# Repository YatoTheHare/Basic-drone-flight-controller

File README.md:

*[PL version]*
# Podstawowy kontroler lotu drona na ESP32-S3-WROOM1

## Opis układu

Jednowarstwowa płytka PCB (z kilkoma przelotkami na zworki łączące wyspy GND).
Układ przeznaczony jest do pełnienia funkcji kontrolera lotu drona czterowirnikowego.
W skład układu wchodzą:
- Port USB-C dla zasilania 5V DC oraz transferu danych
- Mikrokontroler ESP32-S3-WROOM1 z gniazdem JST-SH dla urządzenia peryferyjnego IIC
- Inercyjna 6-osiowa jednostka pomiarowa BMI270
- Układ step-down z 5V na 3,3V - TPS62A02
- Zabezpieczenie łączy danych USB przed wyładowaniami elektrostatycznymi - USBLC6-2SC6
- Dedykowane pady lutownicze dla przewodów ESC

## Cechy układu
- Pojedyncza warstwa PCB: możliwie tanie i proste wykonanie ręczne
- Możliwie kompaktowy rozmiar płytki: minimalizacja powierzchni i masy
- Wygodne umieszczenie złączy (USB-C, JST-SH, ESC)
- Gniazdo USB-C wraz z zabezpieczeniem ESD umieszczone możliwie blisko mikrokontrolera, linie danych daleko od miedzi
- Antena mikrokontrolera poza laminatem: redukcja masy i wymiarów laminatu, brak przeszkody dla sygnału radiowego
- Zastosowanie popularnych wartości rezystorów i kondensatorów: minimalizacja kosztów (brak potrzeby sprowadzania elementów innych niż typowo dostępnych w pracowniach elektronicznych)
- Miejsca wiercenia do montażu w ramie drona
- IMU możliwie blisko środka płytki
- Obsługa pinu PG układu step-down: możliwość uruchomienia procedury awaryjnej lub bezprzewodowego wysłania informacji o położeniu i nachyleniu w przypadku awarii zasilania

## Dobór elementów

### step-down:
- układ: TPS62A02 - węższy zakres napięć odpowiadający wymaganiom, tryb oszczędzania energii, mniejszy pobór prądu, większa częstotliwość pracy
- cewka: 1uH - wg. datasheet
- rezystory pętli zwrotnej: R1 120K + 1,5K, R2 27K - dobrane wg. wzoru z datasheet (R1 = R2(V_out / 0,6V - 1), gdzie R2 <= 100K. Rezystory dobrano z pośród najpopularniejszych wartości w celu minimalizacji kosztów. R2 jest znacznie mniejsze niż podana przez producenta granica akceptowalności szumów.
### protokół komunikacji peryferiów
   IIC (I2C) - protokół działający na jednej wspólnej magistrali niezależnie od liczby urządzeń, komunikacja synchronizowana, mechanizm odpowiedzi ACK, adresacja urządzeń.

### IMU:
   BMI270 niższy poziom szumów, większa odporność na zakłócenia, wibracje i niedoskonałości PCB.

## Propozycje rozwoju układu:
- konstrukcja dwuwarstwowa z osobną warstwą dla GND
- rozszerzenie dostępności złączy dla dodatkowych urządzeń i protokołów komunikacji
- obsługa dodatkowej pamięci wymiennej np. microSD - przechowywanie danych zebranych podczas lotu do późniejszej analizy

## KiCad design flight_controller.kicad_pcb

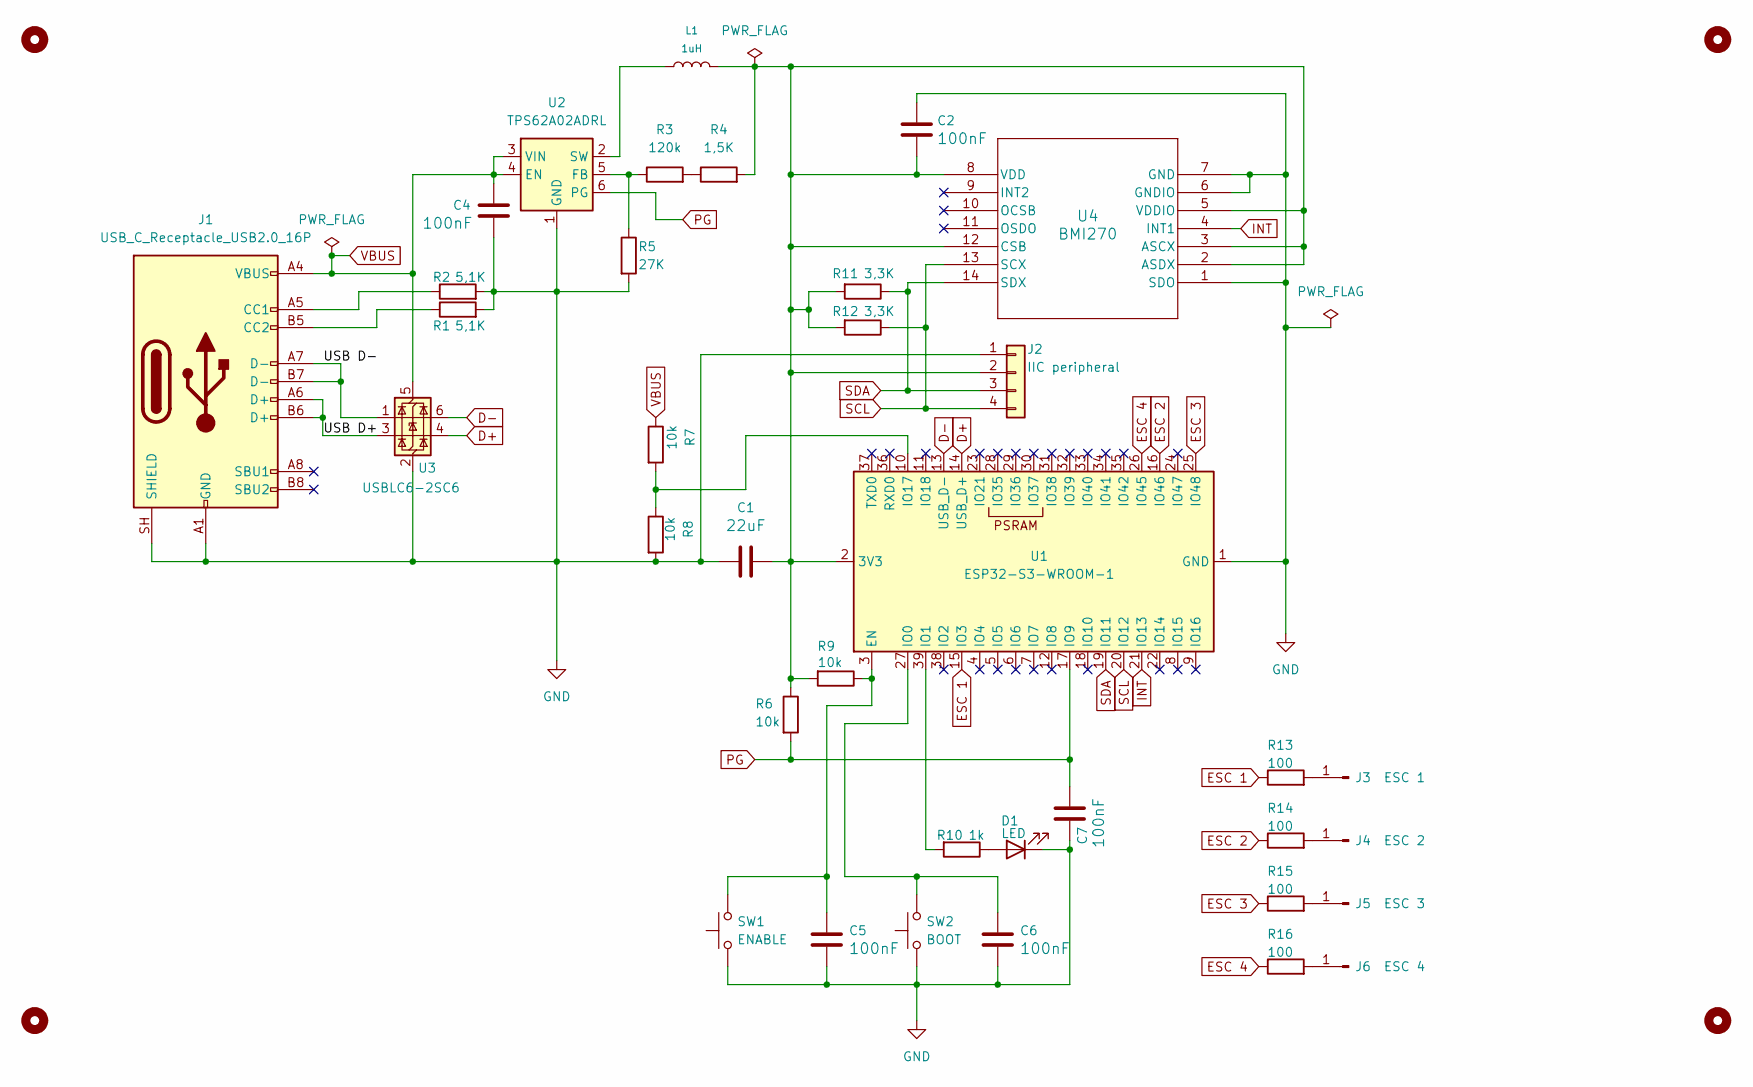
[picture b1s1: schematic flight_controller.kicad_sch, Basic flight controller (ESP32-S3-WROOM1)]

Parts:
C1: 22uF; C_0805_2012Metric_Pad1.18x1.45mm_HandSolder
C2, C4, C5, C6, C7: 100nF; C_0805_2012Metric_Pad1.18x1.45mm_HandSolder
D1: LED; LED_0603_1608Metric
H1, H2, H3, H4: MountingHole; MountingHole_2.1mm
J1: USB_C_Receptacle_USB2.0_16P; USB_C_Receptacle_HRO_TYPE-C-31-M-12
J2: IIC peripheral; JST_SH_SM04B-SRSS-TB_1x04-1MP_P1.00mm_Horizontal
J3: ESC 1; SolderWirePad_1x01_SMD_1.5x3mm
J4: ESC 2; SolderWirePad_1x01_SMD_1.5x3mm
J5: ESC 3; SolderWirePad_1x01_SMD_1.5x3mm
J6: ESC 4; SolderWirePad_1x01_SMD_1.5x3mm
L1: 1uH; L_Taiyo-Yuden_NR-20xx_HandSoldering
R1, R2: 5,1K; R_0402_1005Metric_Pad0.72x0.64mm_HandSolder
R3: 120k; R_0402_1005Metric_Pad0.72x0.64mm_HandSolder
R4: 1,5K; R_0402_1005Metric_Pad0.72x0.64mm_HandSolder
R5: 27K; R_0402_1005Metric_Pad0.72x0.64mm_HandSolder
R6, R7, R8, R9: 10k; R_0402_1005Metric_Pad0.72x0.64mm_HandSolder
R10: 1k; R_0402_1005Metric_Pad0.72x0.64mm_HandSolder
R11, R12: 3,3K; R_0402_1005Metric_Pad0.72x0.64mm_HandSolder
R13, R14, R15, R16: 100; R_0402_1005Metric_Pad0.72x0.64mm_HandSolder
SW1: ENABLE; SW_SPST_PTS647_Sx50
SW2: BOOT; SW_SPST_PTS647_Sx50
U1: ESP32-S3-WROOM-1
U2: TPS62A02ADRL; SOT-563
U3: USBLC6-2SC6; SOT-23-6
U4: BMI270; BMI270_BOS

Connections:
/USB D+: J1.A6 (D+), J1.B6 (D+), U3.3 (I/O2)
/USB D-: J1.A7 (D-), J1.B7 (D-), U3.1 (I/O1)
D+: U1.14 (USB_D+), U3.4 (I/O2)
D-: U1.13 (USB_D-), U3.6 (I/O1)
ESC 1: R13.1, U1.15 (IO3)
ESC 2: R14.1, U1.16 (IO46)
ESC 3: R15.1, U1.25 (IO48)
ESC 4: R16.1, U1.26 (IO45)
GND: C1.1, C2.2, C4.2, C5.1, C6.1, C7.1, D1.1 (K), J1.A1 (GND), J1.A12 (GND), J1.B1 (GND), J1.B12 (GND), J1.SH (SHIELD), J2.1, R1.2, R2.2, R5.2, R8.2, SW1.1, SW2.1, U1.1 (GND), U1.40 (GND), U1.41 (GND), U2.1 (GND), U3.2 (GND), U4.1 (SDO), U4.6 (GNDIO), U4.7 (GND)
INT: U1.21 (IO13), U4.4 (INT1)
unnamed: D1.2 (A), R10.1
unnamed: J1.A5 (CC1), R2.1
unnamed: J1.B5 (CC2), R1.1
unnamed: C1.2, C2.1, J2.2, L1.2, R4.2, R6.1, R9.2, R11.2, R12.2, U1.2 (3V3), U4.2 (ASDX), U4.3 (ASCX), U4.5 (VDDIO), U4.8 (VDD), U4.12 (CSB)
unnamed: J3.1 (Pin_1_1), R13.2
unnamed: J4.1 (Pin_1_1), R14.2
unnamed: J5.1 (Pin_1_1), R15.2
unnamed: J6.1 (Pin_1_1), R16.2
unnamed: R3.2, R4.1
unnamed: C5.2, R9.1, SW1.2, U1.3 (EN)
unnamed: C6.2, SW2.2, U1.27 (IO0)
unnamed: R10.2, U1.39 (IO1)
unnamed: R7.2, R8.1, U1.10 (IO17)
unnamed: R3.1, R5.1, U2.5 (FB)
unnamed: L1.1, U2.2 (SW)
PG: C7.2, R6.2, U1.17 (IO9), U2.6 (PG)
SCL: J2.4, R12.1, U1.20 (IO12), U4.13 (SCX)
SDA: J2.3, R11.1, U1.19 (IO11), U4.14 (SDX)
VBUS: C4.1, J1.A4 (VBUS), J1.A9 (VBUS), J1.B4 (VBUS), J1.B9 (VBUS), R7.1, U2.3 (VIN), U2.4 (EN), U3.5 (VBUS)

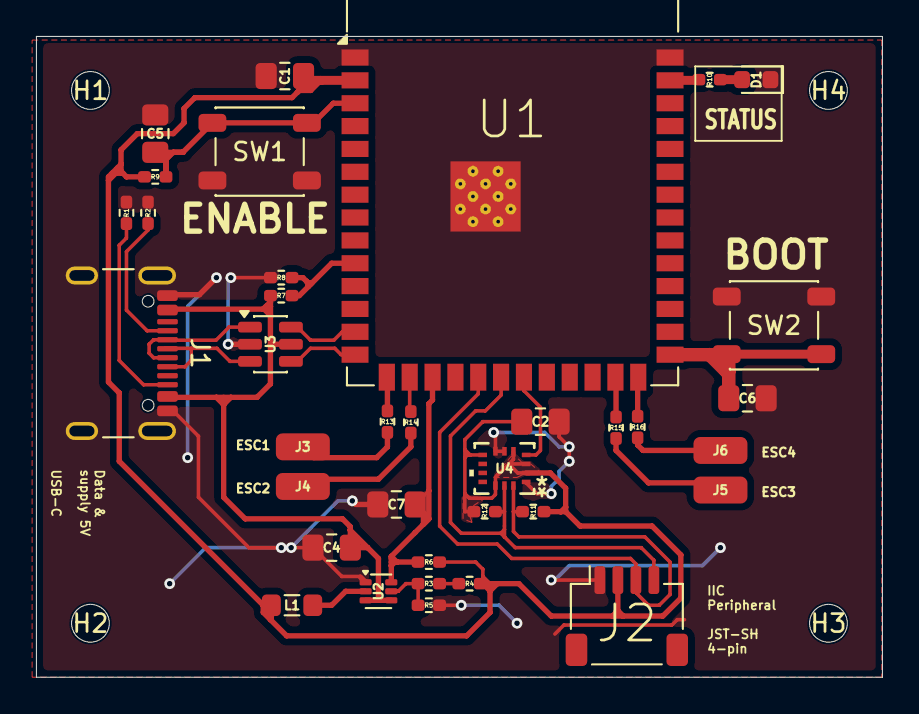
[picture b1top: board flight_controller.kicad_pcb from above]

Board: 2 copper layers, 47.0 x 35.6 mm, 40 parts (0 on the bottom side), 29 nets.
